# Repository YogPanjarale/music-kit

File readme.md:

# Touch Music Kit

Touch Music Kit is an ESP32-based music controller PCB with seven capacitive touch pads, a small OLED display, physical controls, addressable LED output, and a PAM8403 audio amplifier module interface.

## Features

- ESP32-DevKitC module as the main controller.
- Seven on-board capacitive touch pads labeled `S1` through `S7`.
- 0.91 inch SSD1306 I2C OLED module.
- Rotary encoder with integrated push switch.
- Two 12 mm push buttons.
- Slide power switch and power input connectors.
- PAM8403 amplifier module header for audio output.
- Speaker output intended for a 0.5 W, 8 ohm, 32 mm speaker through the PAM8403 module.
- NeoPixel-compatible 3-pin LED header.
- LM1117T-3.3 regulator footprint.
- KiCad project files plus fabrication outputs for board manufacturing.

## Repository Layout

```text
.
|-- hardware/
|   `-- touch-kit/
|       |-- music-kit.kicad_pro
|       |-- music-kit.kicad_sch
|       |-- music-kit.kicad_pcb
|       `-- *_production/
|           `-- dated export folder/
|               |-- Gerber ZIP
|               |-- BOM CSV
|               |-- position CSV
|               `-- IPC netlist
|-- media/
|   `-- pcb-front-render.png
`-- software/
```

The `software/` directory is currently empty.

## Hardware Overview

| Designator | Part / Module | Notes |
| --- | --- | --- |
| `U2` | ESP32-DevKitC | Main controller module. |
| `U3` | ER_OLEDM0.91_1x-I2C | 0.91 inch, 128x32, SSD1306 I2C OLED. |
| `ENC1` | EC11-style rotary encoder | Encoder with push switch. |
| `BT1`, `BT2` | 12 mm push buttons | User input buttons. |
| `J5` | JST-XH 1x08 input connector | Breaks out `S1` through `S7` plus `GND`. |
| `LED1` | 3-pin NeoPixel header | `VCC`, `DATA`, `GND`. |
| `PAM1` | PAM8403 module header | 1x11 header with audio output, DAC input, power, and ground nets. |
| `J4` | 3-pin DAC/audio header | `DAC_OUT`, `VCC`, and `GND`; schematic value is `Speakerdf`. |
| `J1`, `J6` | Power connectors | Auxiliary power and JST-XH power input. |
| `SW1` | Slide switch | Board on/off switch. |
| `U1` | LM1117T-3.3 | 3.3 V regulator footprint. |

The board outline is approximately 134 mm x 75 mm, based on the KiCad edge cuts and dimension markings.

## Firmware Pin Map

This map is derived from the KiCad PCB nets connected to `U2` (`ESP32-DevKitC`).

| Signal | ESP32 GPIO | Purpose |
| --- | ---: | --- |
| `S1` | GPIO4 | Capacitive touch input |
| `S2` | GPIO15 | Capacitive touch input |
| `S3` | GPIO13 | Capacitive touch input |
| `S4` | GPIO14 | Capacitive touch input |
| `S5` | GPIO27 | Capacitive touch input |
| `S6` | GPIO33 | Capacitive touch input |
| `S7` | GPIO32 | Capacitive touch input |
| `DAC_MCU` | GPIO25 | ESP32 DAC/audio signal |
| `WS_DATA` | GPIO26 | NeoPixel data |
| `BT1` | GPIO16 | Push button 1 |
| `BT2` | GPIO17 | Push button 2 |
| `ENC_SW` | GPIO5 | Encoder switch |
| `ENC_DT` | GPIO18 | Encoder data |
| `ENC_CLK` | GPIO19 | Encoder clock |
| `SDA` | GPIO21 | OLED I2C data |
| `SCL` | GPIO22 | OLED I2C clock |

Note: the current PCB silkscreen labels the fifth and sixth input positions as `S6`, `S6`. The KiCad nets show those positions as `S5` and `S6`, so verify the board file before ordering or assembling.

## Manufacturing Files

Open the KiCad project from:

```text
hardware/touch-kit/music-kit.kicad_pro
```

Ready-to-send fabrication outputs are under the production export folder in `hardware/touch-kit/`. The current export can be found with:

```text
hardware/touch-kit/*_production/2026-07-02-17-41-01/
```

That folder includes the Gerber ZIP, BOM CSV, position CSV, and IPC netlist generated from the KiCad PCB. If you change the schematic or PCB, regenerate the manufacturing files from KiCad before ordering.

## Assembly Notes

- Confirm `VCC`, `+BATT`, and `GND` with a multimeter before plugging in the ESP32, OLED, or amplifier module.
- Install the ESP32-DevKitC, OLED, PAM8403 module, buttons, encoder, headers, and power connectors according to the silkscreen and BOM.
- Use the PAM8403 module with the knob-style amplifier header expected by `PAM1`.
- Connect the speaker through the PAM8403 module output pins marked `SP+` and `SP-`; do not assume `J4` is the raw speaker output without checking the board file.
- The NeoPixel header `LED1` is labeled `VCC`, `DATA`, `GND`; data is driven by `WS_DATA` / GPIO26.

## Firmware Status

Firmware is not included yet. A firmware project should initialize:

- ESP32 capacitive touch readings for `S1` through `S7`.
- SSD1306 display over I2C on GPIO21/GPIO22.
- Audio or DAC output on GPIO25.
- NeoPixel output on GPIO26.
- Button and encoder inputs on GPIO16, GPIO17, GPIO5, GPIO18, and GPIO19.

## License

This project is licensed under the MIT License. See [LICENSE](LICENSE).

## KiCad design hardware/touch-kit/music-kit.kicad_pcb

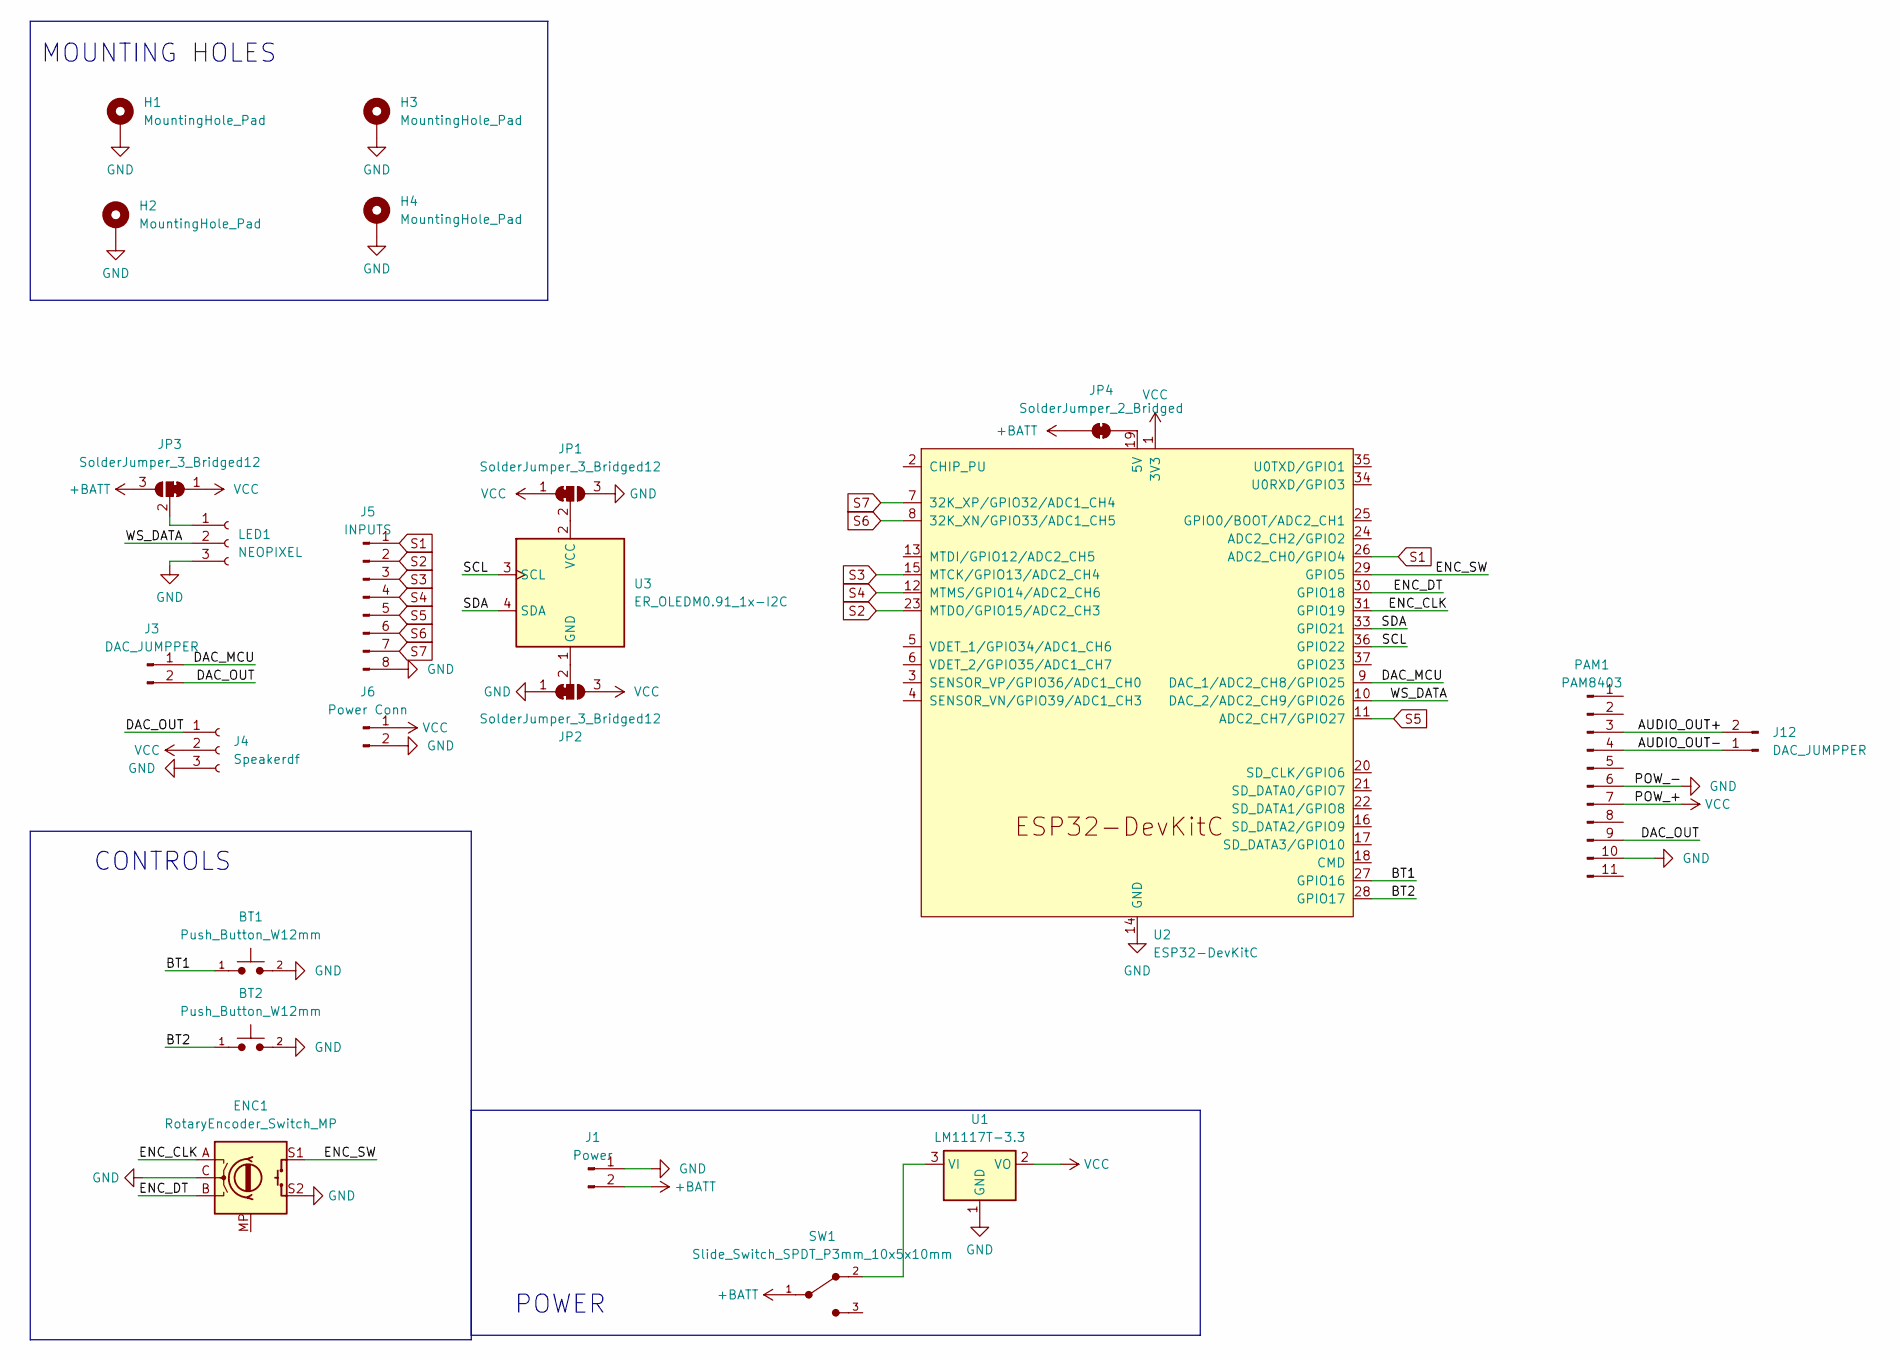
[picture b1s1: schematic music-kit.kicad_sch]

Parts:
BT1, BT2: Push_Button_W12mm
ENC1: RotaryEncoder_Switch_MP; RotaryEncoder_Alps_EC11E-Switch_Vertical_H20mm
H1, H2, H3, H4: MountingHole_Pad; MountingHole_3.2mm_M3_DIN965_Pad
J1: Power; PinSocket_1x02_P2.54mm_Horizontal
J3, J12: DAC_JUMPPER; PinHeader_1x02_P2.54mm_Vertical
J4: Speakerdf; PinSocket_1x03_P2.54mm_Vertical
J5: INPUTS; JST_XH_B8B-XH-A_1x08_P2.50mm_Vertical
J6: Power Conn; JST_XH_B2B-XH-A_1x02_P2.50mm_Vertical
JP1, JP2, JP3: SolderJumper_3_Bridged12; SolderJumper-3_P1.3mm_Bridged12_Pad1.0x1.5mm
JP4: SolderJumper_2_Bridged; SolderJumper-2_P1.3mm_Bridged_Pad1.0x1.5mm
LED1: NEOPIXEL; PinSocket_1x03_P2.54mm_Vertical
PAM1: PAM8403; PinHeader_1x11_P2.54mm_Vertical
SW1: Slide_Switch_SPDT_P3mm_10x5x10mm
U1: LM1117T-3.3; TO-220-3_Horizontal_TabDown
U2: ESP32-DevKitC
U3: ER_OLEDM0.91_1x-I2C

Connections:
+BATT: J1.2, JP3.3 (B), JP4.1 (A), SW1.1
/AUDIO_OUT+: J12.2, PAM1.3
/AUDIO_OUT-: J12.1, PAM1.4
/BT1: BT1.1, U2.27 (GPIO16)
/BT2: BT2.1, U2.28 (GPIO17)
/DAC_MCU: J3.1, U2.9 (DAC_1/ADC2_CH8/GPIO25)
/DAC_OUT: J3.2, J4.1, PAM1.9
/ENC_CLK: ENC1.A, U2.31 (GPIO19)
/ENC_DT: ENC1.B, U2.30 (GPIO18)
/ENC_SW: ENC1.S1, U2.29 (GPIO5)
/SCL: U2.36 (GPIO22), U3.3 (SCL)
/SDA: U2.33 (GPIO21), U3.4 (SDA)
/WS_DATA: LED1.2, U2.10 (DAC_2/ADC2_CH9/GPIO26)
GND: BT1.2, BT2.2, ENC1.C, ENC1.S2, H1.1 (1_1), H2.1 (1_1), H3.1 (1_1), H4.1 (1_1), J1.1, J4.3, J5.8, J6.2, JP1.3 (B), JP2.1 (A), LED1.3, PAM1.6, PAM1.10, U1.1 (GND), U2.14 (GND), U2.32 (GND), U2.38 (GND)
unnamed: JP1.2 (C), U3.2 (VCC)
unnamed: JP2.2 (C), U3.1 (GND)
unnamed: JP3.2 (C), LED1.1
unnamed: JP4.2 (B), U2.19 (5V)
unnamed: SW1.2, U1.3 (VI)
S1: J5.1, U2.26 (ADC2_CH0/GPIO4)
S2: J5.2, U2.23 (MTDO/GPIO15/ADC2_CH3)
S3: J5.3, U2.15 (MTCK/GPIO13/ADC2_CH4)
S4: J5.4, U2.12 (MTMS/GPIO14/ADC2_CH6)
S5: J5.5, U2.11 (ADC2_CH7/GPIO27)
S6: J5.6, U2.8 (32K_XN/GPIO33/ADC1_CH5)
S7: J5.7, U2.7 (32K_XP/GPIO32/ADC1_CH4)
VCC: J4.2, J6.1, JP1.1 (A), JP2.3 (B), JP3.1 (A), PAM1.7, U1.2 (VO), U2.1 (3V3)

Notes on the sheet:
POWER
CONTROLS
MOUNTING HOLES

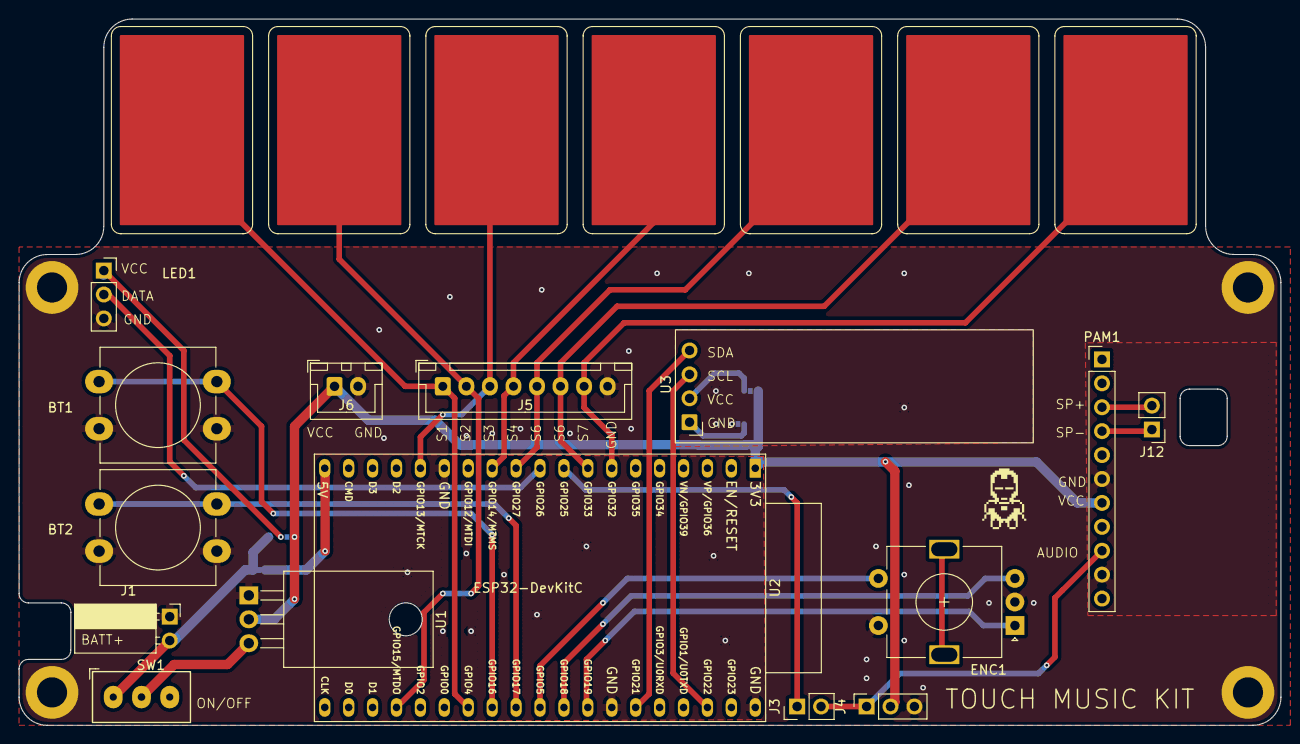
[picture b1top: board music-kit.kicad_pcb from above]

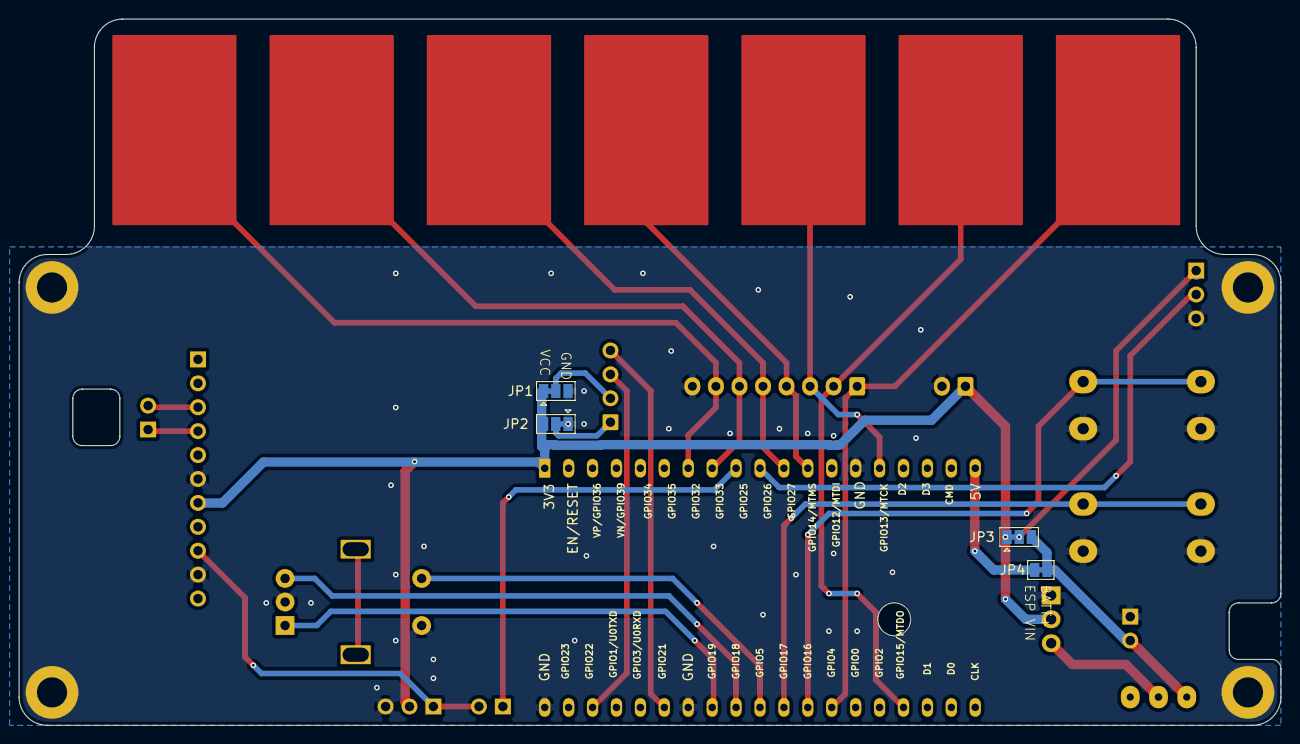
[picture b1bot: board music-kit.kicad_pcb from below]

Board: 2 copper layers, 134.0 x 75.0 mm, 23 parts (4 on the bottom side), 27 nets.

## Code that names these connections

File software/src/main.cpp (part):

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 *                  releases when let go (only Capacitive/Digital press-hold).
 *   - Percussion : drum-style noise+pitch hit, one-shot.
 *
 * Rotary encoder menu:  GPIO5 = SW   GPIO18 = CLK   GPIO19 = DT
 * Scale buttons:        GPIO16 = DOWN (prev)   GPIO17 = UP (next)
 *   Wire each button between the pin and GND (internal pull-ups are used).
 *
 * Audio renders in small chunks in loop() between scans, so notes ring out
 * continuously without blocking input.
 *
 * Board: ESP32-DevKitC. DAC = GPIO25 -> PAM8403 -> speaker. Serial @ 115200.
 */

#include <Arduino.h>
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const int NUM = 7;
// Pad order follows the PCB net map S1..S7 (see readme "Firmware Pin Map").
const uint8_t PAD_PIN[NUM] = {
    4,   // S1: GPIO4  / touch T0
    15,  // S2: GPIO15 / touch T3
    13,  // S3: GPIO13 / touch T4
    14,  // S4: GPIO14 / touch T6
    27,  // S5: GPIO27 / touch T7
    33,  // S6: GPIO33 / touch T8
    32   // S7: GPIO32 / touch T9
};

// Capacitive touch detection with hysteresis: touchRead returns LOWER when touched.
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const int BTN_PIN[2] = { 16, 17 };   // [0] = DOWN/prev, [1] = UP/next

// Rotary encoder (active LOW switch, internal pull-ups)
const int ENC_SW_PIN  = 5;
const int ENC_CLK_PIN = 18;
const int ENC_DT_PIN  = 19;
const bool ENCODER_REVERSE = false;  // flip if clockwise feels backwards

// 0.91" OLED (SSD1306, 128x32) on I2C: SDA=21, SCL=22, address 0x3C
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Adafruit_SSD1306 display(128, 32, &Wire, -1);
bool oledOK = false;

// NeoPixel pin-activity display: one RGB LED per pad on GPIO26 (PCB WS_DATA net).
// LED index matches pad index; active pads stay lit, triggers flash briefly.
const int LED_PIN   = 26;
const int LED_COUNT = NUM;
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void showScaleButtonAction(int buttonIndex) {
  menuIdx = MENU_SCALE;
  menuEditing = false;
  scaleButtonMsg = buttonIndex == 0 ? "GPIO16 DOWN" : "GPIO17 UP";
  scaleButtonMsgUntil = millis() + 900;
}

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// ---- Rotary encoder: rotate selects/edits, switch toggles edit mode ----
void scanEncoder() {
  uint32_t now = millis();
  int clk = digitalRead(ENC_CLK_PIN);
  if (clk != encLastClk) {
    if (clk == LOW) {
      int delta = (digitalRead(ENC_DT_PIN) != clk) ? +1 : -1;
      if (ENCODER_REVERSE) delta = -delta;
      handleEncoderTurn(delta);
    }
    encLastClk = clk;
  }

  bool swPressed = (digitalRead(ENC_SW_PIN) == LOW);
  if (swPressed && !encSwWas && (now - encSwLast) > 180) {
    menuEditing = !menuEditing;
    drawMenu();
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
  pinMode(BTN_PIN[0], INPUT_PULLUP);
  pinMode(BTN_PIN[1], INPUT_PULLUP);
  pinMode(ENC_SW_PIN, INPUT_PULLUP);
  pinMode(ENC_CLK_PIN, INPUT_PULLUP);
  pinMode(ENC_DT_PIN, INPUT_PULLUP);
  encLastClk = digitalRead(ENC_CLK_PIN);

  dacWrite(DAC_PIN, DC_MID);

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  } else {
    Serial.println("digital mode: comparator/LDR/switch output to pad GPIO; active HIGH with internal pulldowns");
  }
  Serial.println("scale buttons: GPIO16 = down, GPIO17 = up");
  Serial.println("rotary: GPIO5 = switch, GPIO18 = CLK, GPIO19 = DT");
  Serial.printf("NeoPixel pin activity: %d LEDs on GPIO%d\n", LED_COUNT, LED_PIN);

  playScaleIntro();
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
